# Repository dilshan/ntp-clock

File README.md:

# NTP based digital clock panel

This project introduces an open-source, *ATmega328* based, configurable [NTP](https://en.wikipedia.org/wiki/Network_Time_Protocol) clock with a 2.3-inch, 7-segment display driver. This clock automatically obtains time from the configured NTP server and updates the date and time of the built-in RTC (*real-time clock*). If the connection to the NTP server is lost, the clock continues to run using its built-in RTC.

All the parameters of this clock can configure using its USB base serial terminal. The firmware of this clock supports both *static* and *DHCP* addressing modes. Apart from that, parameters such as NTP server address, time-offset, and clock display formats can change through the menu-driven configuration terminal.

This clock is designed to drive large common-anode, 7-segment displays. The prototype version is assembled using four individual segments of 7.2V, 2.3-inch, red color displays (*FJS23101BH*). To archive, the necessary high output voltage and the current, the 7-segment display output stage of this clock is formed using *ULN2803* Darlington transistor array and *BC858* transistors.

The network component of this clock is built around the *ENC28J60* 10BASE-T stand-alone Ethernet controller.

Highly accurate *DS3231M* RTC is using in this clock for time-keeping operations. To backup the date and time, the *CR1220* type button cell is included in the PCB. The date and time are syncs with the NTP server during the system startup. Users can manually initiate synchronization by pressing the "*SYNC*" button in the system.

Depending on the NTP server, the user needs to specify the time offset to the system to get the correct local time. Time offset can configure using the system configuration menu, and it must be input in a standard format like *+5:30*.

Firmware of this clock is developed using the [Arduino framework](https://www.arduino.cc/en/software) and libraries.

[**PCBWay**](https://www.pcbway.com) provides sponsorship for this project. The [PCBWay online ordering service](https://www.pcbway.com/orderonline.aspx) provides excellent help to fabricate this PCB. We got finished PCBs within three days, and the quality of the service is at a superior level. PCB of this project can directly [order from PCBWay through this link](https://www.pcbway.com/project/shareproject/NTP_based_digital_clock_panel.html).

This project is a [certified](https://certification.oshwa.org/lk000009.html) open-source hardware project. All the content of this project are distributed under the terms of the following license:

- Hardware License: [CC BY 4.0](https://creativecommons.org/licenses/by/4.0/)
- Software and firmware License: [MIT](https://github.com/dilshan/ntp-clock/blob/main/LICENSE)
- [Documentation](https://github.com/dilshan/ntp-clock/wiki) License: [CC BY 4.0](https://creativecommons.org/licenses/by/4.0/)

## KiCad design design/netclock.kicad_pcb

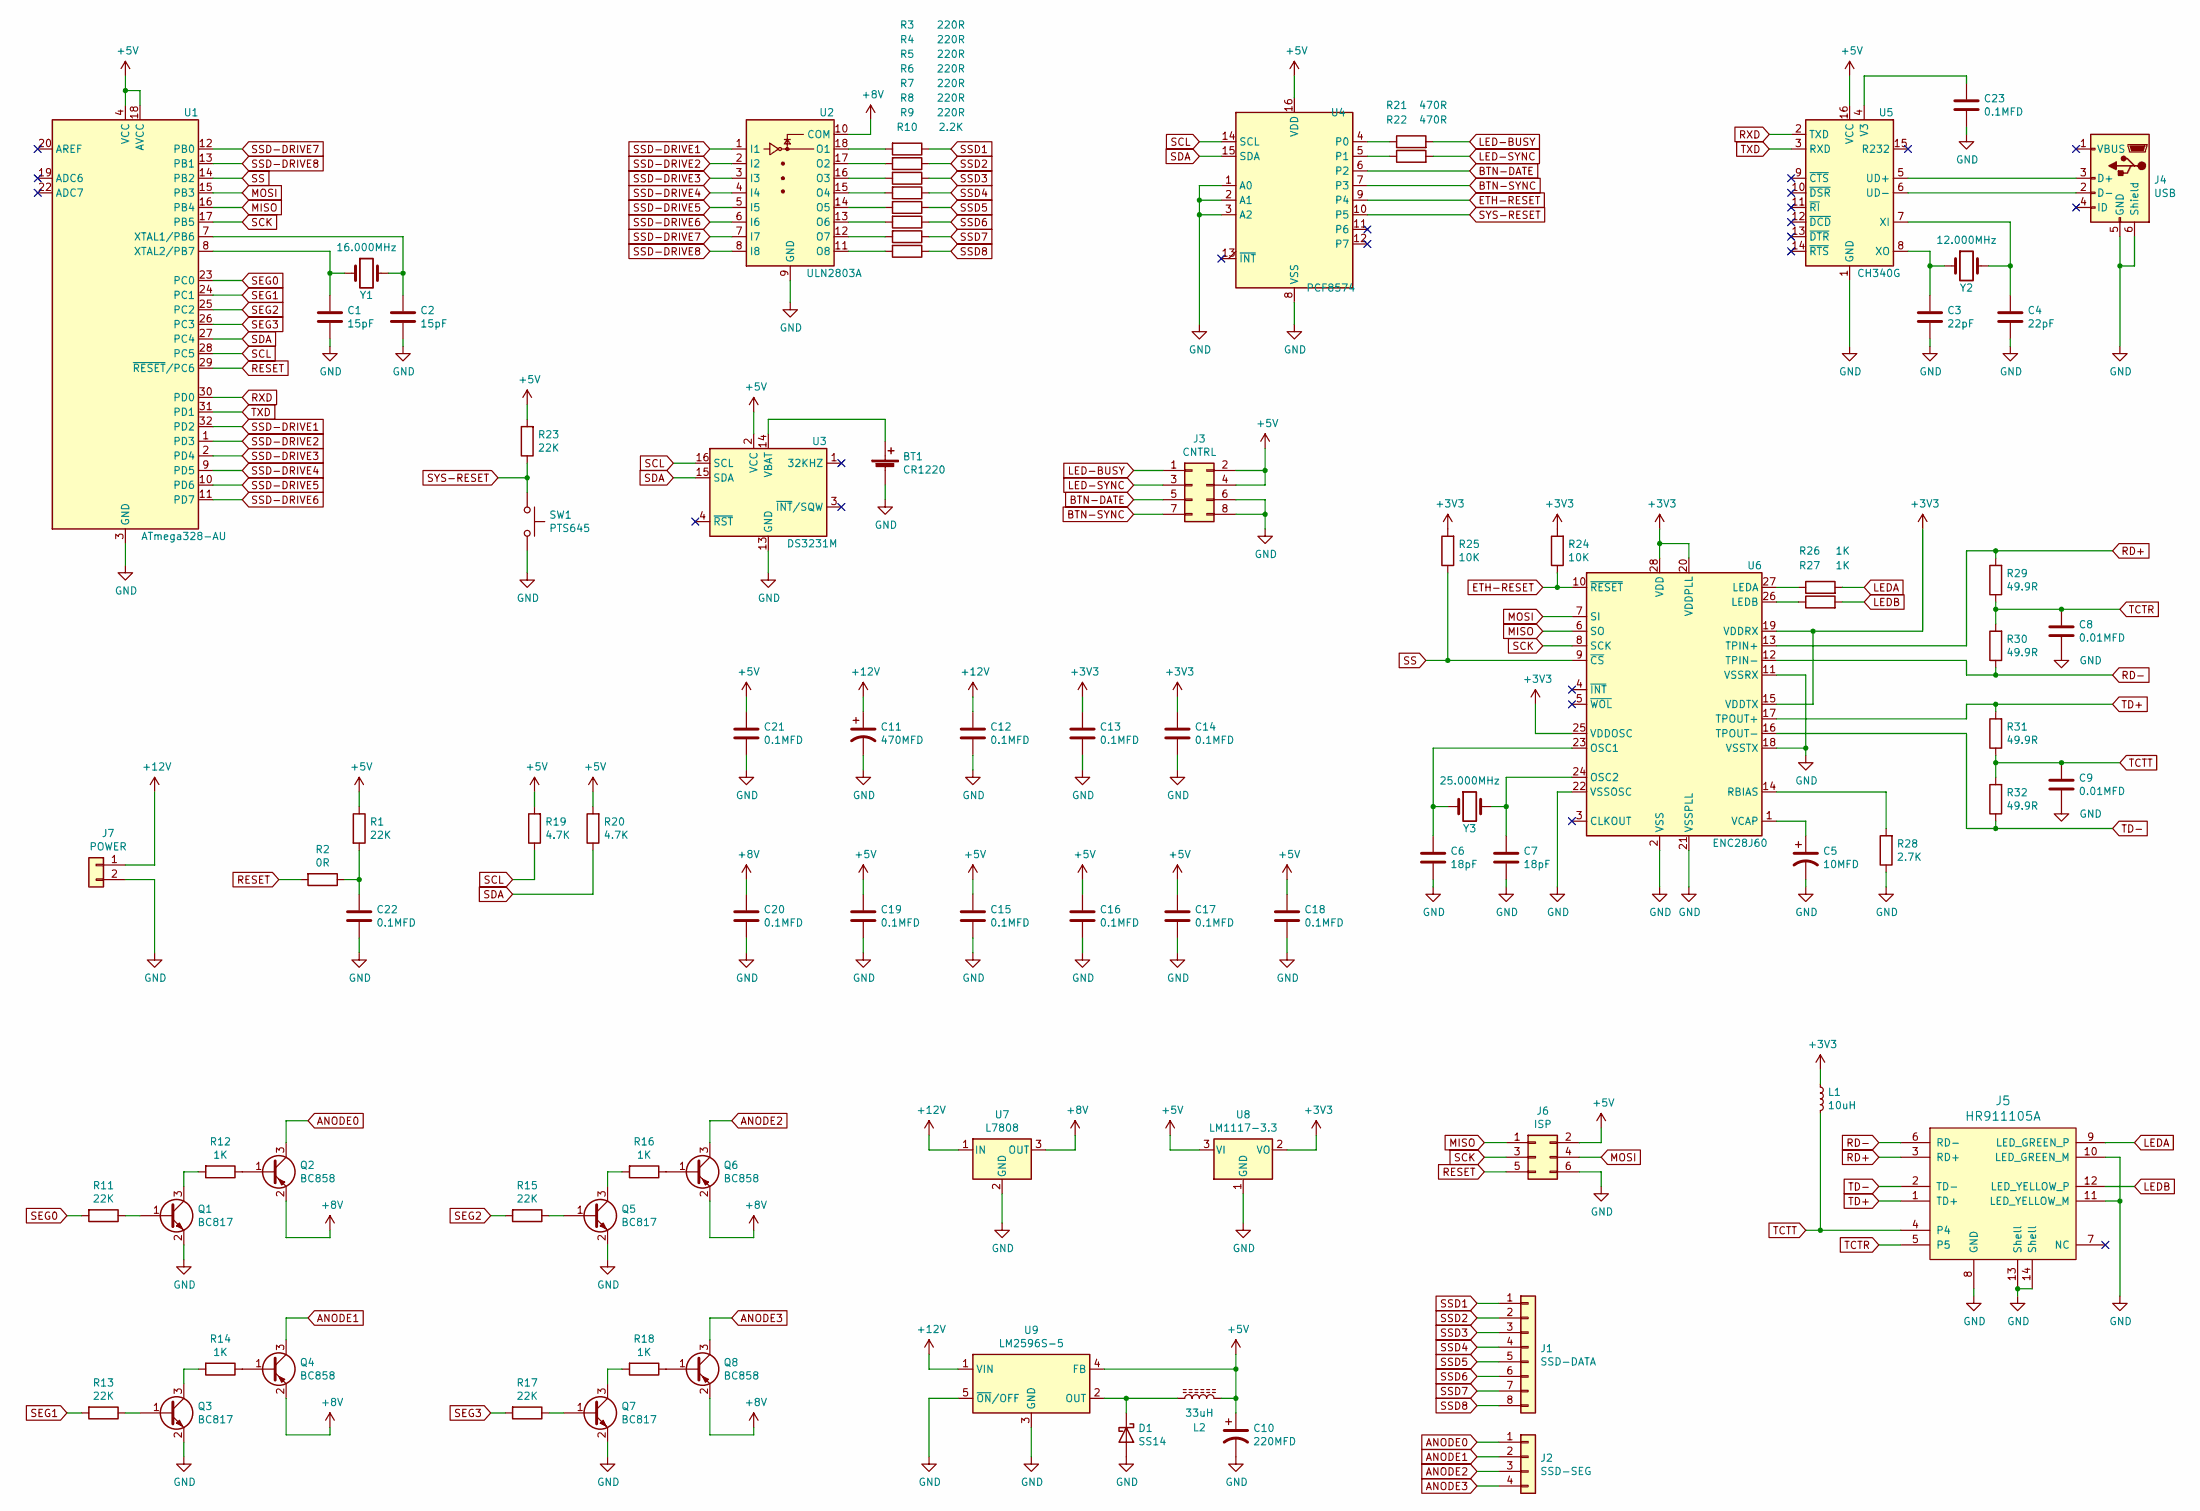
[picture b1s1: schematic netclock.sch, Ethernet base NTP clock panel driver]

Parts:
BT1: CR1220; BAT_BC501SM
C1, C2: 15pF; C_0805_2012Metric_Pad1.15x1.40mm_HandSolder
C3, C4: 22pF; C_0805_2012Metric_Pad1.15x1.40mm_HandSolder
C5: 10MFD; CP_EIA-3216-18_Kemet-A_Pad1.58x1.35mm_HandSolder
C6, C7: 18pF; C_0805_2012Metric_Pad1.15x1.40mm_HandSolder
C8, C9: 0.01MFD; C_0805_2012Metric_Pad1.15x1.40mm_HandSolder
C10: 220MFD; CP_Radial_D8.0mm_P5.00mm
C11: 470MFD; CP_Radial_D10.0mm_P5.00mm
C12: 0.1MFD; C_Disc_D7.5mm_W5.0mm_P5.00mm
C13, C14, C15, C16, C17, C18, C19, C21, C22, C23: 0.1MFD; C_0805_2012Metric_Pad1.15x1.40mm_HandSolder
C20: 0.1MFD; C_Disc_D6.0mm_W4.4mm_P5.00mm
D1: SS14; D_SMA
J1: SSD-DATA; PinHeader_1x08_P2.54mm_Vertical
J2: SSD-SEG; PinHeader_1x04_P2.54mm_Vertical
J3: CNTRL; PinHeader_2x04_P2.54mm_Vertical
J4: USB; USB_Mini-B_Lumberg_2486_01_Horizontal
J5: HR911105A; HR911105a
J6: ISP; PinHeader_2x03_P2.54mm_Vertical
J7: POWER; PhoenixContact_MCV_1,5_2-G-3.5_1x02_P3.50mm_Vertical
L1: 10uH; L_0805_2012Metric_Pad1.15x1.40mm_HandSolder
L2: 33uH; L_10.4x10.4_H4.8
Q1, Q3, Q5, Q7: BC817; SOT-23
Q2, Q4, Q6, Q8: BC858; SOT-23
R1, R11, R13, R15, R17, R23: 22K; R_0805_2012Metric_Pad1.15x1.40mm_HandSolder
R2: 0R; R_0805_2012Metric_Pad1.15x1.40mm_HandSolder
R3, R4, R5, R6, R7, R8, R9: 220R; R_0805_2012Metric_Pad1.15x1.40mm_HandSolder
R10: 2.2K; R_0805_2012Metric_Pad1.15x1.40mm_HandSolder
R12, R14, R16, R18, R26, R27: 1K; R_0805_2012Metric_Pad1.15x1.40mm_HandSolder
R19, R20: 4.7K; R_0805_2012Metric_Pad1.15x1.40mm_HandSolder
R21, R22: 470R; R_0805_2012Metric_Pad1.15x1.40mm_HandSolder
R24, R25: 10K; R_0805_2012Metric_Pad1.15x1.40mm_HandSolder
R28: 2.7K; R_0805_2012Metric_Pad1.15x1.40mm_HandSolder
R29, R30, R31, R32: 49.9R; R_0805_2012Metric_Pad1.15x1.40mm_HandSolder
SW1: PTS645; SW_Tactile_SPST_Angled_PTS645Vx31-2LFS
U1: ATmega328-AU; TQFP-32_7x7mm_P0.8mm
U2: ULN2803A; SOIC-18W_7.5x11.6mm_P1.27mm
U3: DS3231M; SOIC-16W_7.5x10.3mm_P1.27mm
U4: PCF8574; SOIC-16W_7.5x10.3mm_P1.27mm
U5: CH340G; SOIC-16_3.9x9.9mm_P1.27mm
U6: ENC28J60; SSOP-28_5.3x10.2mm_P0.65mm
U7: L7808; TO-252-3_TabPin2
U8: LM1117-3.3; SOT-223-3_TabPin2
U9: LM2596S-5; TO-263-5_TabPin3
Y1: 16.000MHz; Crystal_HC49-U_Vertical
Y2: 12.000MHz; Crystal_HC49-U_Vertical
Y3: 25.000MHz; Crystal_HC49-U_Vertical

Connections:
+3V3: C13.1, C14.1, L1.1, R24.2, R25.2, U6.15 (VDDTX), U6.19 (VDDRX), U6.20 (VDDPLL), U6.25 (VDDOSC), U6.28 (VDD), U8.2 (VO)
+5V: C10.1, C15.1, C16.1, C17.1, C18.1, C19.1, C21.1, J3.2, J3.4, J6.2, L2.2, R1.1, R19.2, R20.2, R23.2, U1.4 (VCC), U1.6 (VCC), U1.18 (AVCC), U3.2 (VCC), U4.16 (VDD), U5.16 (VCC), U8.3 (VI), U9.4 (FB)
+8V: C20.1, Q2.2 (E), Q4.2 (E), Q6.2 (E), Q8.2 (E), U2.10 (COM), U7.3 (OUT)
+12V: C11.1, C12.1, J7.1, U7.1 (IN), U9.1 (VIN)
ANODE0: J2.1, Q2.3 (C)
ANODE1: J2.2, Q4.3 (C)
ANODE2: J2.3, Q6.3 (C)
ANODE3: J2.4, Q8.3 (C)
BTN-DATE: J3.5, U4.6 (P2)
BTN-SYNC: J3.7, U4.7 (P3)
ETH-RESET: R24.1, U4.9 (P4), U6.10 (~RESET)
GND: BT1.2 (-), C1.2, C2.2, C3.2, C4.2, C5.2, C6.2, C7.2, C8.2, C9.2, C10.2, C11.2, C12.2, C13.2, C14.2, C15.2, C16.2, C17.2, C18.2, C19.2, C20.2, C21.2, C22.2, C23.2, D1.2 (A), J3.6, J3.8, J4.5 (GND), J4.6 (Shield), J5.8 (GND), J5.10 (LED_GREEN_M), J5.11 (LED_YELLOW_M), J5.13 (Shell), J5.14 (Shell), J6.6, J7.2, Q1.2 (E), Q3.2 (E), Q5.2 (E), Q7.2 (E), R28.1, SW1.2, U1.3 (GND), U1.5 (GND), U1.21 (GND), U2.9 (GND), U3.5 (GND), U3.6 (GND), U3.7 (GND), U3.8 (GND), U3.9 (GND), U3.10 (GND), U3.11 (GND), U3.12 (GND), U3.13 (GND), U4.1 (A0), U4.2 (A1), U4.3 (A2), U4.8 (VSS), U5.1 (GND), U6.2 (VSS), U6.11 (VSSRX), U6.18 (VSSTX), U6.21 (VSSPLL), U6.22 (VSSOSC), U7.2 (GND), U8.1 (GND), U9.3 (GND), U9.5 (~ON~/OFF)
LED-BUSY: J3.1, R21.2
LED-SYNC: J3.3, R22.2
LEDA: J5.9 (LED_GREEN_P), R27.2
LEDB: J5.12 (LED_YELLOW_P), R26.2
MISO: J6.1, U1.16 (PB4), U6.6 (SO)
MOSI: J6.4, U1.15 (PB3), U6.7 (SI)
unnamed: BT1.1 (+), U3.14 (VBAT)
unnamed: C1.1, U1.8 (XTAL2/PB7), Y1.1
unnamed: C2.1, U1.7 (XTAL1/PB6), Y1.2
unnamed: C3.1, U5.8 (XO), Y2.1
unnamed: C4.1, U5.7 (XI), Y2.2
unnamed: C5.1, U6.1 (VCAP)
unnamed: C6.1, U6.23 (OSC1), Y3.1
unnamed: C7.1, U6.24 (OSC2), Y3.2
unnamed: C22.1, R1.2, R2.1
unnamed: C23.1, U5.4 (V3)
unnamed: D1.1 (K), L2.1, U9.2 (OUT)
unnamed: J4.2 (D-), U5.6 (UD-)
unnamed: J4.3 (D+), U5.5 (UD+)
unnamed: Q1.1 (B), R11.1
unnamed: Q1.3 (C), R12.2
unnamed: Q2.1 (B), R12.1
unnamed: Q3.1 (B), R13.1
unnamed: Q3.3 (C), R14.2
unnamed: Q4.1 (B), R14.1
unnamed: Q5.1 (B), R15.1
unnamed: Q5.3 (C), R16.2
unnamed: Q6.1 (B), R16.1
unnamed: Q7.1 (B), R17.1
unnamed: Q7.3 (C), R18.2
unnamed: Q8.1 (B), R18.1
unnamed: R3.2, U2.18 (O1)
unnamed: R4.2, U2.17 (O2)
unnamed: R5.2, U2.16 (O3)
unnamed: R6.2, U2.15 (O4)
unnamed: R7.2, U2.14 (O5)
unnamed: R8.2, U2.13 (O6)
unnamed: R9.2, U2.12 (O7)
unnamed: R10.2, U2.11 (O8)
unnamed: R21.1, U4.4 (P0)
unnamed: R22.1, U4.5 (P1)
unnamed: R26.1, U6.26 (LEDB)
unnamed: R27.1, U6.27 (LEDA)
unnamed: R28.2, U6.14 (RBIAS)
RD+: J5.3 (RD+), R29.2, U6.13 (TPIN+)
RD-: J5.6 (RD-), R30.1, U6.12 (TPIN-)
RESET: J6.5, R2.2, U1.29 (~RESET~/PC6)
RXD: U1.30 (PD0), U5.2 (TXD)
SCK: J6.3, U1.17 (PB5), U6.8 (SCK)
SCL: R19.1, U1.28 (PC5), U3.16 (SCL), U4.14 (SCL)
SDA: R20.1, U1.27 (PC4), U3.15 (SDA), U4.15 (SDA)
SEG0: R11.2, U1.23 (PC0)
SEG1: R13.2, U1.24 (PC1)
SEG2: R15.2, U1.25 (PC2)
SEG3: R17.2, U1.26 (PC3)
SS: R25.1, U1.14 (PB2), U6.9 (~CS)
SSD1: J1.1, R3.1
SSD2: J1.2, R4.1
SSD3: J1.3, R5.1
SSD4: J1.4, R6.1
SSD5: J1.5, R7.1
SSD6: J1.6, R8.1
SSD7: J1.7, R9.1
SSD8: J1.8, R10.1
SSD-DRIVE1: U1.32 (PD2), U2.1 (I1)
SSD-DRIVE2: U1.1 (PD3), U2.2 (I2)
SSD-DRIVE3: U1.2 (PD4), U2.3 (I3)
SSD-DRIVE4: U1.9 (PD5), U2.4 (I4)
SSD-DRIVE5: U1.10 (PD6), U2.5 (I5)
SSD-DRIVE6: U1.11 (PD7), U2.6 (I6)
SSD-DRIVE7: U1.12 (PB0), U2.7 (I7)
SSD-DRIVE8: U1.13 (PB1), U2.8 (I8)
SYS-RESET: R23.1, SW1.1, U4.10 (P5)
TCTR: C8.1, J5.5, R29.1, R30.2
TCTT: C9.1, J5.4, L1.2, R31.1, R32.2
TD+: J5.1 (TD+), R31.2, U6.17 (TPOUT+)
TD-: J5.2 (TD-), R32.1, U6.16 (TPOUT-)
TXD: U1.31 (PD1), U5.3 (RXD)

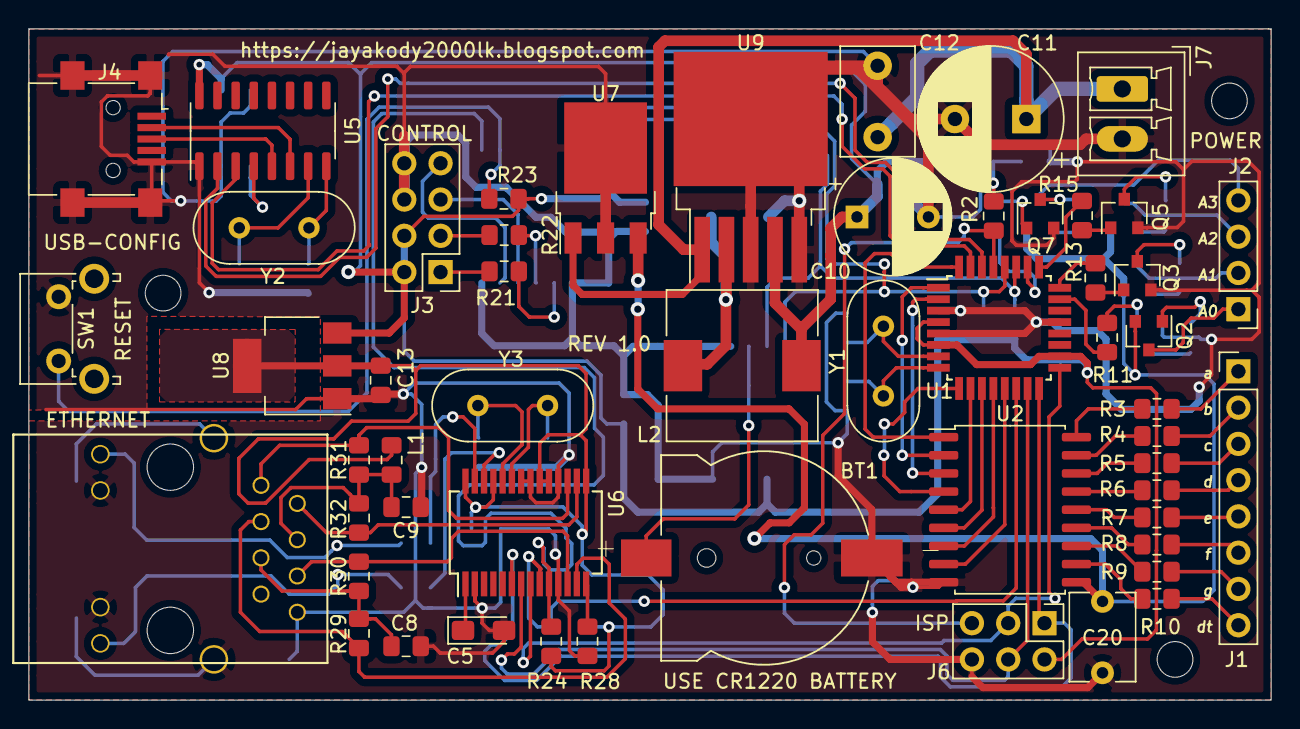
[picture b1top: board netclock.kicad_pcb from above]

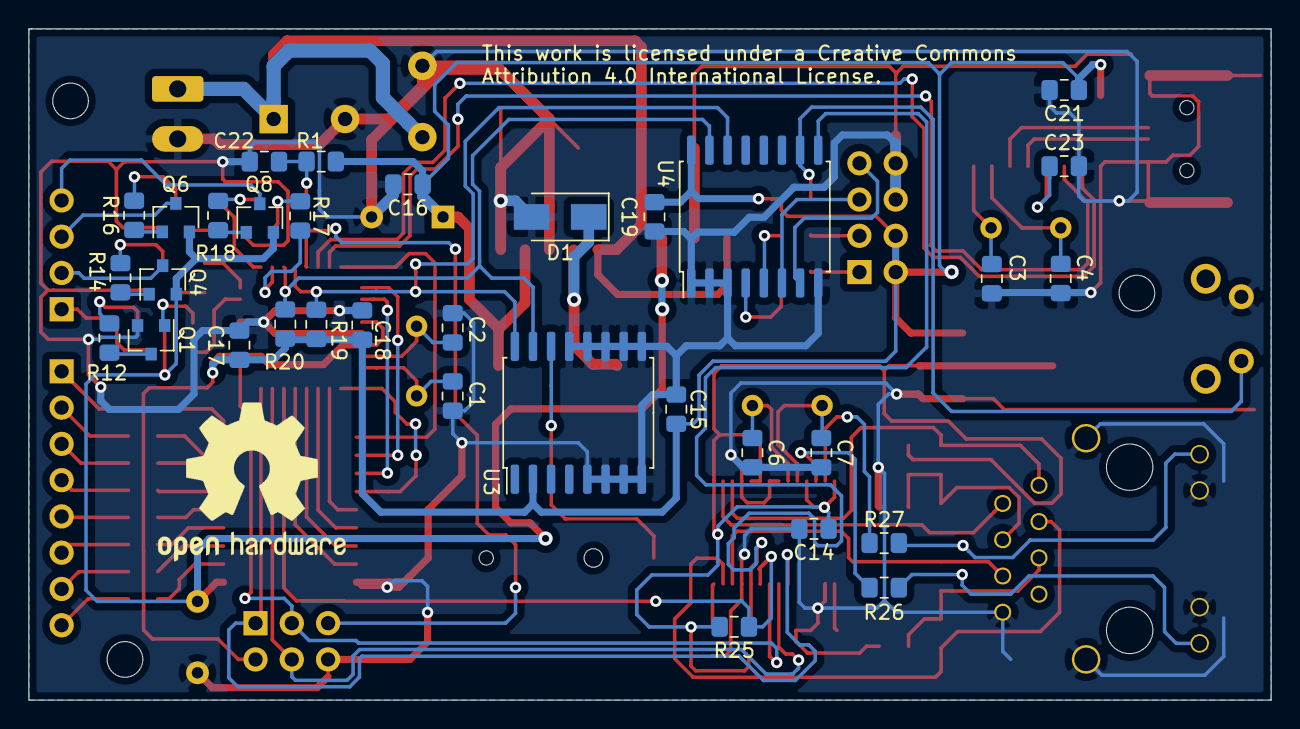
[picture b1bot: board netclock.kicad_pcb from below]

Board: 2 copper layers, 87.0 x 47.0 mm, 91 parts (34 on the bottom side), 90 nets.

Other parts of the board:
 : OSHW-Logo2_14.6x12mm_SilkScreen
 #2,  #3,  #4: MountingHole_2.5mm

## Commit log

2021-04-26 Initial version of NTP clock driver source code and design files.
2021-04-26 Add prototype image the readme.md file.
2021-04-27 Add NTP clock driver connection diagram.
2021-04-27 Update 7-segment display details in the wiring layout.
2021-04-27 Add PDF version of wiring layout.
2021-04-27 Add wiki link into the documentation section.
2021-04-27 Add link to the PCBWay store.
2021-05-13 Update readme.md with OSHWA certificate link :books:

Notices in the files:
design/netclock.kicad_pcb:
This work is licensed under a Creative Commons
Attribution 4.0 International License.
